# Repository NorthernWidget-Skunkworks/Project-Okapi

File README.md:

# Okapi: Data logger with integrated solar charging and modular telemetry

***Okapi data logger (Resnik v0.4.0), with a micro-SD card for local storage and a Particle Boron telemetry module.***

The **Okapi** data logger responds to the need for a robust, flexible, and power-efficient open-source option to record and transmit data from remote locations. It is programmable using the open-source standard Arduino framework via a standard micro-USB cable and supports a wide range of sensor input/output options. It connects to dual power supplies to ensure consistent recordings, and interfaces with a range of “Feather”-form-factor boards for telemetry.

## Namesake

The Okapi, a relative of the giraffe, communicates over long distances using [infrasound](https://en.wikipedia.org/wiki/Infrasound). The telemetry capabilities of this data logger inspired this namesake.

## Technical specifications

### Electronic Hardware

* Microcontroller (computer) core
  * ATMega1284p
  * Arduino compatible
  * Programmable using C++
  * 8 MHz
* Real-time clock
  * DS3231M
  * Temperature-compensated crystal for high accuracy (±5 ppm)
* Sensor and general-purpose connections
  * Primary Rail (selectable 3.3V or 5V)
    * I2C (up to 128 sensors permitted; expansion ports provided by Project Heptapod)
    * SPI
    * 2x 16-bit analog
    * Analog voltage reference
    * 12-bit Digital-to-analog conversion
    * 2x General-purpose input/output
    * USART
    * 2x Vbus (selectable 3.3V or 5V)
    * 2x Ground
  * Secondary Rail (selectable 3.3V or 5V)
    * I2C (up to 128 sensors permitted; expansion ports provided by Project Heptapod)
    * 2x 16-bit analog
    * 2x General-purpose input/output
    * USART
    * 2x Vbus (selectable 3.3V or 5V)
    * 2x Ground
* Data storage and return
  * Local storage: micro SD card
  * Telemetry: support for Feather-profile boards, including Particle devices:
    * Mobile phone networks
    * WiFi
    * Bluetooth
    * [In development] Iridium satellite
* Power
  * Dual power supply
  * Primary Power
    * Built-in maximum-power-point-tracking solar-charge-control circuitry
    * Lithium-Ion battery
  * Backup Power
    * Alkaline AA batteries
  * Real-time clock
    * Coin cell
  * Power consumption
    * Primary power, sleeping: 80 μA
    * Backup power, sleeping: 4 μA
    * Active (typical: data logger without sensors): 10 mA
    * Transmitting (mobile networks, typical: Particle Boron):
      * 16 mA background
      * 40 mA burst
  * Power generation
  * Solar, low light: 100 mA
* User interface
  * “Log” button: instantaneous reading (for testing)
  * “Reset” button
  * 2x 3-color indicator LEDs
  * Computer readout via a serial monitor, included in the Arduino software
* Open-source licensing via CC BY-SA 4.0

>> @bschulz1701: Any updates needed? I think that there is also a WDT (correct?)

### Electronic Software and Firmware

* Programmable using the Arduino IDE https://www.arduino.cc/en/main/software
* Custom bootloader and board definition for ATMega1284p available via https://github.com/NorthernWidget/Arduino_Boards
* Custom libraries from Northern Widget and the open-source community
  * Primary data-logger functions
  * Libraries available with each sensor, exposing a standard interface
* Open-source licensing via GNU GPL 3.0

### Pinout and board interfaces

***Okapi data logger (Resnik v0.4.0) with pins, connectors, and interactive items annotated.***

**Pins are colored following this convention:**
* Ground: black
* Power supply: red
* Universal Serial Asynchronous Receiver--Transmitter (USART or UART): blue
* General-purpose I/O pins: gray
* Analog inputs and associated reference voltage: green
* Digital communications buses (SPI and I2C): purple
* Analog adjustable voltage output: salmon

**The power and programming connectors at the "south" end of the board are as follows:**
* Micro-USB connector
  * The same connector as many Android and other mobile phones at the time of writing; may be programmed using any USB cable for these that is not charging-only (i.e. that can carry data)
  * Can be used with our [clock-setting program](https://github.com/NorthernWidget/SetTime_GUI) to set the time on the real-time clock.
  * Provides power to the data logger while it is connected; this power source is isolated from the batteries and solar panel, and therefore may be plugged in safely at any time.
* Solar panel, 4.95--32.0 V. A wide range of panels can work with this.
* Li-Ion battery, 2.60--4.475 V. This works with standard 18650 Li-ion batteries. It can work well with just a single battery, but if more storage is required, multiple 18650 batteries may be connected in parallel; we have a circuit-board design to do this: https://github.com/NorthernWidget/LiIon-18650-Parallel. ***CAUTION***: most commercially available multiple-18650-battery holders connect them in series; this voltage is ***TOO HIGH*** for the data logger.
* Primary batteries. This is ideally a pack of 3 primary (i.e., not reusable) Alkaline (or better) AA batteries with a long shelf life. The Okapi data logger will switch to these if its rechargeable power supply shuts down. The internal electronics reduce the quiescent power consumption while under backup power (see the above list of [electronic hardware technical specifications](#electronic-hardware)) and inform the logger about which power supply is being used, allowing it to, for example, reduce or temporarily terminate data transmission.

>> @bschulz1701: Solar panel supply current / size?

**"RST" and "LOG" buttons:**
* Reset ("RST"): stop the program that is currently executing on the main logger and return it to its boot sequence.
* Log Now ("LOG"): take a reading immediately. This is useful for diagnoses and testing.

>> General note: we may want to have an LED flash whenever the logger takes a reading -- even for 1/10 of a second. With an option to disable this, of course. But it is often better to know while in the field that a system is working

**Other notes, clockwise from the top:**
* The socket holds a [Feather-form-factor board](https://learn.adafruit.com/adafruit-feather/feather-specification).
  * This standard, designed by [Adafruit](https://www.adafruit.com/), has been widely adopted, including by the IoT/telemetry module designer [Particle](https://www.particle.io/).
  * We often use a [Particle Boron mobile-phone telemetry unit](https://docs.particle.io/boron/).
* Mounting holes for [\#4 screws](https://www.mcmaster.com/91772A106/)
* CR1220 battery; can power the real-time clock for up to 7 years
* ISP header (also called an ICSP header): This 3x2 header is used with an in-system programmer (in-circuit system programmer) to upload the (bootloader)[#installing-the-bootloader] to the data logger.
* A micro-SD card holds a copy of all data, whether or not any telemetry is used

>> @bschulz1701: check my clock 7-year figure

***Okapi data logger (Resnik v0.4.0) with key microchips, LEDs, and switches marked.*** *MCU: Microcontroller. RTC: Real-time clock. LED: Light-emitting diode. Bus: a subsystem for connections and data transfer.*

The Okapi data logger contains two buses (see above), each of which has an independent voltage. The primary bus is on the left and the secondary bus is on the right. These can be selected as 3.3V (switches slid towards the inside of the board) or 5V (switches towards the outside of the board).

>> @bschulz1701: How much power can each bus source/sink?

Two LEDs, status and auxiliary, flash messages to the user to provide information on proper operations vs. a variety of possible errors. These are useful for field diagnoses, and are further described in [the field guide section, below](#field-guide).

>> Design note: move STAT label to left of LED so it can be better seen

The Li-ion override button, which can be pressed with the tip of a pen or other small object, ...

>> @bschulz1701: This somehow overrides the Li-Ion battery electronics to allow something to happen... but I am not remembering what!

## On-board Devices

### I2C

| **Device**                                                        	| **Default address** 	| **Reprogrammable address** 	| **Function**                                                     	|
|-------------------------------------------------------------------	|---------------------	|----------------------------	|------------------------------------------------------------------	|
| [DS3231](https://github.com/NorthernWidget/DS3231_Logger)         	| 0x68                	| N                          	| Real-time clock                                                  	|
| [MCP23018](https://github.com/NorthernWidget-Skunkworks/MCP23018) 	| 0x20                	| N                          	| I/O Expander                                                     	|
| [ADS1115](https://github.com/adafruit/Adafruit_ADS1X15)           	| 0x48                	| N                          	| ADC (on-board devices)                                           	|
| [ADS1115](https://github.com/adafruit/Adafruit_ADS1X15)           	| 0x49                	| N                          	| ADC (off-board devices)                                          	|
| [MCP4725](https://github.com/NorthernWidget-Skunkworks/MCP4725)   	| 0x62                	| N                          	| DAC                                                              	|
| [BME280](https://github.com/NorthernWidget/BME_Library)           	| 0x77                	| N                          	| On-board barometric pressure, temperature, and relative humidity 	|

### SPI

* SD Card

### UART (USART)

* FTDI USB-Serial converter
* Feather form-factor telemetry board; typically [Particle Boron](https://docs.particle.io/boron/)

## Assembly

Assembling this data logger is possible by hand with sufficient skill and the following tools:
* Temperature-controlled soldering iron
* Hot-air rework station
* Equipment for stenciling with solder paste
* ESD-safe tweezers and workstation
* Solder wick

Mechanized assembly by a professional circuit-board assembly house, which is available in many parts of the world, may be preferred due to the complexity of this data logger board.

>> THOUGHT: I have basic instructions for assembly on the [Project Walrus](https://github.com/NorthernWidget-Skunkworks/Project-TPDH-Walrus) README; I will not reproduce these here just yet, as we might want to set up a separate assembly guide, mostly with good links to existing resources, since our writing something of this nature would be to reinvent the wheel.

## Programming

### Downloading and installing the Arduino IDE

Go to https://www.arduino.cc/en/main/software. Choose the proper IDE version for your computer. For Windows, we suggest the non-app version to have more control over Arduino; this might change in the future. You will have to add custom libraries, so the web version will not work (at least, as of the time of writing). Download and install the Arduino IDE. Open it to begin the next steps.

### Installing the bootloader

Before a data logger can receive programs via the convenient USB port, it must have a *bootloader* that tells it to expect to receive new programs that way.  You can read more about bootloaders in general here: https://www.arduino.cc/en/Hacking/Bootloader.

Because you can't upload the bootloader via USB, you use the 2x3-pin 6-pin ICSP (also called ISP) header with a special device called an "in-circuit system programmer" (or just "in-system programmer; yup, that's what the acronym stands for).

Many devices exist to upload a bootloader including:
* The official [AVR ISP mkII](http://ww1.microchip.com/downloads/en/DeviceDoc/Atmel-42093-AVR-ISP-mkII_UserGuide.pdf) (no longer produced but available used)
* Using an [Arduino as an ISP](https://www.arduino.cc/en/tutorial/arduinoISP)
* The versatile [Olimex AVR-ISP-MK2](https://www.olimex.com/Products/AVR/Programmers/AVR-ISP-MK2/open-source-hardware)
* The [Adafruit USBtinyISP](https://www.adafruit.com/product/46)

To upload the bootloader, do the following:

1. Open the Arduino IDE. If you have not yet installed the Northern Widget board definitions, find and install them here (instructions provided): https://github.com/NorthernWidget/Arduino_Boards
2. Select the desired board -- most likely ***ATMega1284p 8MHz*** under *Northern Widget Boards*.
3. Plug the data logger into your computer via a micro-USB cable to provide power.
4. Plug your ISP of choice into your computer (via a USB cable) and onto the 6-pin header. There are two ways to place it on; the header is aligned such that the ribbon cable should be facing away from the board while programming. If this fails without being able to upload, try flipping the header around.
5. Go to Tools --> Programmer and select the appropriate programmer based on what you are using.
6. Go to Tools --> Burn bootloader. Typically, within a few seconds, you learn whether you succeeded or failed. Hopefully it worked!

***Important note for Linux users:*** You must supply permissions to the Arduino IDE for it to be able to use the ICSP, or you will have to run it using `sudo`. The former option is better; the latter is easier in the moment.

***Note: Be sure to download and/or update drivers for your ISP.***

### Installing the requisite software libraries

>> @awickert: Add a full list of the requisite software to install; finish the firmware aggregator and use those directions (or the Arduino ones) to help users install that + sdfat. Include screenshots and host those directions at https://github.com/NorthernWidget-Skunkworks/Firmware-Aggregator.

### How to write a program

The below program is an example that you can copy and paste directly into the Arduino IDE in order to upload to your data logger. We'll walk you through what each piece of the code is and does.

#### Full program
```c++
/*
 * Okapi example: connected with a Walrus pressure--temperature sensor, often
 * used for water-level measurements, via the Longbow I2C/RS-485 translator.
 * Written by Bobby Schulz with a few comments added by Andy Wickert.
 */

#include "Okapi.h"
#include <TP_Downhole_Longbow.h>

TP_Downhole_Longbow Walrus; // Instantiate Walrus sensor; relict library name
Okapi Logger; // Instantiate data logger object

String Header = ""; // Information header; starts as an empty string
uint8_t I2CVals[1] = {0x22}; // I2C addresses of sensors

unsigned long UpdateRate = 60; // Number of seconds between readings

void setup() {
  Header = Header + Walrus.GetHeader();
  Logger.begin(I2CVals, sizeof(I2CVals), Header); // Pass header info to logger
  Init();
}

void loop() {
  Logger.run(Update, UpdateRate);
}

String Update()
{
  Init();
  delay(1500);
  return Walrus.GetString();
}

void Init()
{
  Walrus.begin(13, 0x22); // Instantiate Walrus (at address = 13)
                          // and Longbow Widget (at address = 0x22)
}
```

#### "Include" statements

```c++
#include "Okapi.h"
#include <TP_Downhole_Longbow.h>
```

These bring in the two code libraries involved, the former for the data logger and the latter for the sensors. This allows the user to access the classes and functions within these two libraries, as we will show in more detail below.

#### Instantiate a sensor object

```c++
TP_Downhole_Longbow Walrus; // Instantiate Walrus sensor; relict library name
Okapi Logger; // Instantiate data logger object
```

"Instantiating an object" means that we create our own specific versions of the a class of items. This can be thought of as: `Breakfast myBreakfast`. Breakfast is the general concept, but I create "myBreakfast", which I can then modify. In this same way, "Logger" is what we call our Okapi data logger, and "Walrus" is what we call our "TP_Downhole_Longbow" sensor; this name is a holdover from an earlier design that is the ancestor of the Walrus. We can then access functions and variables within these two instantiated objects.

#### Declare the header string

```c++
String Header = ""; // Information header; starts as an empty string
```

We start with an empty header, but will soon add information to it.

#### Create a list of the I2C addresses of the sensors

```c++
uint8_t I2CVals[1] = {0x22}; // I2C addresses of sensors
```

This is the trickiest step. You need to know what the I2C address of your sensor is. You can skip this, but then the logger will not run a check to see if the sensor is properly connected.

>> Let's make sure that we record this one each page, or find a way to replace this.

#### Declare the amount of time between logging events

```c++
unsigned long UpdateRate = 60; // Number of seconds between readings
```

This is the number of seconds between logging events. If it takes 2 seconds to record data, make sure that you give the logger at least 3 seconds between events. The maximum logging time is set by the watchdog timer, which [FINISH HERE]

>> @BSCHULZ1701: Is there an external WDT on Okapi?

#### `setup()` step: runs once at the start

```c++
void setup() {
  Header = Header + Walrus.GetHeader();
  Logger.begin(I2CVals, sizeof(I2CVals), Header); //Pass header info to logger
  Init();
}
```

`setup()` is a special function that runs just once when the logger boots up. In this case, it first adds the Walrus' header to the header string. `GetHeader()` is a standard function that lies within each of our sensor libraries and returns this header information as a `String`. We then pass the header and the I2C values to the Okapi library's `begin()` function. This sets up the header and prepares the data loger to record data. Finally, this function calls `Init()`, which we skip ahead to describe immediately below.

>> (awickert): I still don't understand why we have to pass `sizeof()` and can't just compute that within the function.

#### `Init()` function: skipping ahead to understand `setup()`

```c++
void Init()
{
  Walrus.begin(13, 0x22); // Instantiate Walrus (at address = 13)
                          // and Longbow Widget (at address = 0x22)
}
```

The `Init()` function calls the `begin()` function, standard within each Northern Widget sensor library, to instantiate the connection ports (e.g., I2C, RS-485) used to communicate between the sensor and the logger. In this case, there is only one sensor, but two ports are needed: An RS-485 signal goes from the Walrus to the Longbow Widget, which then converts the signal into an I2C signal with its own address. The reason for this is that an I2C signal can travel only ~3 m, but an RS-485 signal can travel ~100 m.

#### `loop()` step: keeps running until stopped

```c++
void loop() {
  Logger.run(Update, UpdateRate);
}
```

The loop calls the main function of the Okapi library, `run()`, repeatedly. This puts the logger into a low-power sleep mode and wakes it up only when interrupted by the clock or the "LOG" button. `Update` refers to the function described immediately below. `UpdateRate` is our logging interval defined above.

#### `Update()` function: Gives data for the logger to record

```c++
String Update()
{
  Init();
  delay(1500);
  return Walrus.GetString();
}
```

The `Update()` function first calls the `Init()` function to be sure that the sensor is ready to log. It then in this case delays 1500 milliseconds; this is an ad-hoc solution to the question of how long it takes the pressure transducer to settle after being started up, and is a safe large amount of time. This function then can `return` a string of all of the Walrus' readings (one pressure and two temperature measurements) separated by commas. This is then concatenated to a list of logger-internal measurements -- date/time; on-board temperature, pressure, and relative humidity; and onboard voltages for battery and solar-panel status -- and recorded to the SD card. If telemetry were present, these data could also be sent to a remote location.

### Reference

A full index of the public variables and functions within the Okapi data logger library is available at https://github.com/NorthernWidget/Okapi_Library.

>> Send user to library page

>> Thoughts: We should make all comments compatible with doxygen (following) what I did with the ALog library. It also looks like TravisCI has support for Arduino(!) This means that we could also automate construction of the documentation for these libraries.

### Integration with Particle Boron

>> @bschulz1701?

## Wiring

>> Example needed

## Power supply

* **Lithium-ion 18650 rechargeable batteries**; this board can hold two in parallel: https://github.com/NorthernWidget/LiIon-18650-Parallel
* **Solar panel**. A wide range is acceptable, but we like [Voltaic Systems' 6-watt panel](https://voltaicsystems.com/6-watt-panel/). If you do not want to snip off the barrel jack, [this extension plug from Adafruit should work](https://www.adafruit.com/product/2788) (though we have not tested it... and you'll also have to cut *it* in half).
* **Primary alkaline batteries**; we typically use three high-quality (e.g., Duracell) AAs. These are the backup power supply, and we place them in a [3xAA holder (in series for the proper voltage) with a switch](https://www.jameco.com/z/SBH-331-AS-R-3x-AA-Battery-Holder-with-Cover-and-Switch_216144.html).

>> @bschulz1701: new smarter 18650 holder?

## Housing

The below suggestions encompass what we use and suggest for the housing. In the end, any sufficiently waterproof enclosure will work.

### Materials

* **Enclosure**: [PolyCase WH-16-03 outdoor-rated hinged enclosure](https://www.polycase.com/wh-16)
* **Cable glands**: [RDC07AA](https://www.elecdirect.com/catalogsearch/result/?q=RDC07AA). One per sensor, plus one for the solar panel.
>> AW: Photo didn't take; look up
* **Fasteners**
  * [M5-0.8 x 10 mm truss head screws](https://www.mcmaster.com/92467A320/) x4 to attach mounting plate to threaded inserts in the enclosure
  * [\#4-40 x 1/4 in pan head screws](https://www.mcmaster.com/91772A106/) x22 to attach Okapi, battery packs, and mounting plate to standoffs
  * [\#4-40 x 2 in Female Threaded Hex Standoffs](https://www.mcmaster.com/91115A173/) x3 to stand off Okapi from mounting plate
  * [\#4-40 x 1/2 in Female Threaded Hex Standoffs](https://www.mcmaster.com/91920A533/) x8 to stand off AA battery pack and Li-Ion battery pack from mounting plate
* **Mounting plate for Okapi** (Milled, ABS)
  * [Mounting Plate Design](Mounting%20Plate)
* **Power**
>> Solar panel
  * [3x AA battery pack BK-1280-PC6](https://www.digikey.com/en/products/detail/mpd-memory-protection-devices/BK-1280-PC6/1640076) for alkaline battery backup, mounting holes included for #4-40 screws
>> Li-Ion battery and holder

### Tools

* CNC mill and/or drill press
* Deburring tool or knife + skill and patience
* Torque wrench(es) for 1.0, 1.2 N m

### Assembly

>> Guide with photos. Perhaps ask @superchap123 to use his CNC

>> Placeholder for Now

>> Also include information on passing wiring through

## Field operator's guide

### Initialize
1. Ensure that all connections are secure and SD card is inserted
2. Turn battery pack on
3. Wait for GREEN - GREEN - 5x Blue Flash
	- If you see this, the logger is properly recording data. To double-check, go to "Check"
	- If you see a different flash pattern, go to "Error"

### Check
1. After going through "Initialize", wait 2-3 minutes
2. Follow the instructions in the "Download" section
3. Check to make sure that all the data are being recorded at the proper (UTC) time
4. Check that valid values are being recorded for sensors
7. Whether or not files are properly recorded, return to "Initialize"
	- If files are not recorded, replace the SD card, check all connections, turn the logger back
	  on, and try again
	- If there is an issue with a specific sensor, check connections and troubleshoot
	- If files are recorded properly, return to Initilaize and do not return to "Check"

### SD card swap
1. Turn battery pack off
2. Remove SD card. Ensure that it is labeled. Put it somewhere safe and memorable
3. Replace the SD card with an equivalently labeled SD card
4. Go to "Initialize"

### Download
1. Turn battery pack off
2. Remove SD card
3. Insert SD card in computer
4. Navigate in the SD card to the most recent "log" file (NW→<serial_number>→Log<number>.txt)
5. Save the data file in a well-labeled and organized place.
6. Safely eject the SD card from the computer
7. Go to "Initialize"

### Error

#### Status Codes

The first LED (AUX) will turn green so long as power is applied.
The second LED (STAT) will have one of the colors below.

**Green:**: All systems check out OK, logging will proceed

**Orange:**: A sensor system is not registering properly, some sensor data may be missing or incorrect
* Verify correct polarity of sensor connection
* Ensure the right sensor is connected
* Verify the screw terminals are well connected to the wires (a loose connection can cause a failure)
* Make sure battery power is applied, some sensors can fail otherwise

**Cyan:**: Clock time is incorrect, but logger is otherwise working correctly
* Connect the logger to a computer and reset the clock using the Northern Widget Time Set GUI
* Start Processing
* Open the Northern Widget Time Set program
* Note and record the wrong time if the logger has been out in the field, alongside the current (correct) time, to correct the prior measurements
* Click the "set time" button and check that you are <3 seconds off of the correct time
* Click the "close" button

**Pink**: (looks like purple to some people): SD card is not inserted
* Insert the SD card, or remove and re-insert to make sure card is fully seated

**Red**: Critical on board component is not functioning correctly, such as SD card or clock; Logging will likely not be able to proceed
* Attempt power cycle
* Try different SD card
* Disconnect all sensors; reconnect one by one and check

**Yellow, Fast Blinking**: <50% battery capacity
* Replace batteries: turn battery pack off, replace batteries, and turn battery pack back on

**Red, Fast Blinking**: Batteries <3.3V. Voltage too low to properly function
* Replace batteries: turn battery pack off, replace batteries, and turn battery pack back on.

#### General tips to solve many kinds of errors
* Turn the the logger off and on
* Verify the quality of all screw terminal connections by gently tugging on the wires and making sure they stay in place, if not, remove, replace, and re-tighten the connection
* Ensure sensors and/or cables are not damaged, this can result is shorts or other problems
* Make sure batteries have sufficient voltage to run the logger (>3.3 V)

## NW-Device-Specification schema

Okapi's serial number scheme is [Schema 0](https://github.com/NorthernWidget/NW-Device-Specification) — the same 8-byte EEPROM block used by Margay, predating the formal specification. Schema 1 formalizes it as Page 0 and defines a putative Page 1 for the case where Okapi communicates its status to a higher-level device (e.g., the Particle Boron telemetry board). **Okapi has no current peripheral interface; Page 1 is hypothetical.**

Over I²C this would follow the standard register-addressed read. Over UART (the current Okapi↔Boron link) a framing layer is required; see the [NW-Device-Specification transport section](https://github.com/NorthernWidget/NW-Device-Specification) for the Magic Preamble and COBS options.

### Current EEPROM serial number (Schema 0)

Eight bytes at `EEPROM[length−8]` through `EEPROM[length−1]`, big-endian uint16 per field, written by the setup sketch `SN Set` command — identical scheme to Margay:

| Bytes | Field | Example (Okapi v1.0) |
|-------|-------|----------------------|
| 0–1 | Board type | `0x4F01` (`'O'` = 0x4F, revision 1) |
| 2–3 | Group ID | operator-assigned |
| 4–5 | Unique ID | monotonically increasing |
| 6–7 | FirmwareID | `0x0000` (hardcoded) |

Legacy units manufactured as "Resnik" carry board type `0x9950`.

### Proposed register layout (NW-Device-Specification Schema 1)

**Page 0 (0x00–0x1F) — Identity (EEPROM)**

```
Block 0 (0x00–0x07)   Core identity
  0x00        0x01                          Schema (NW-Device-Specification v1)
  0x01–0x05   'O','k','a','p','i'           Device name (5 bytes)
  0x06–0x07   0x00,0x00                     Reserved

Block 1 (0x08–0x0F)   Version
  0x08        HW major
  0x09        HW minor
  0x0A        FW patch
  0x0B–0x0D   0x00,0x00,0x00               Unused (combined repo convention)
  0x0E–0x0F   0x00,0x00                    Reserved

Block 2 (0x10–0x17)   Serial number
  0x10–0x11   0x4F,0x01                    Board type ('O'=0x4F, revision index)
  0x12–0x13   [manufacture]                Group ID
  0x14–0x15   [manufacture]                Unique ID
  0x16–0x17   0x00,0x00                    FirmwareID (legacy, reserved)

Block 3 (0x18–0x1F)   Integrity + administration
  0x18–0x1C   0x00 ×5                      Reserved
  0x1D        0x00                         Magic byte (reserved; purpose TBD)
  0x1E        [computed]                   CRC-8 of bytes 0x00–0x1D
  0x1F        0x00                         Peripheral address (unassigned;
                                           Okapi is currently controller only)
```

**Page 1 (0x20–0x3F) — Logger status (SRAM) — HYPOTHETICAL**

Okapi is currently an I²C controller communicating with the Particle Boron via UART; it has no peripheral interface. This layout is proposed for the case where Okapi reports status to the Boron (or any higher-level device) using the NW schema. A natural peripheral address would be `0x4F` (ASCII `'O'`).

Okapi's dual power system (LiPo primary + solar charging + AA backup) differs from Margay. Full power monitoring signals are not yet implemented in the library (`GetPowerStats()` is reserved); fields marked TBD will be defined when that work is completed.

```
Block 0 (0x20–0x27)   System status + power
  0x20        Status       bit 0=ready, bit 1=SD fault, bit 2=RTC fault,
                           bit 3=onboard fault, bit 4=sensor fault,
                           bit 5=LiPo warning, bit 6=LiPo error,
                           bit 7=backup warning
  0x21        LiPo %       uint8, 0–100
  0x22–0x23   LiPo voltage uint16, 0.01 V
  0x24–0x25   Solar input  uint16, TBD (V or mW pending GetPowerStats() impl.)
  0x26–0x27   Backup volt  uint16, 0.01 V (AA backup rail)

Block 1 (0x28–0x2F)   BME280 — onboard environment
  0x28–0x29   Temperature  int16, 0.01 °C
  0x2A–0x2B   Humidity     uint16, 0.01 %RH
  0x2C–0x2F   Pressure     uint32, 0.01 hPa

Block 2 (0x30–0x37)   DS3231M — RTC
  0x30–0x33   Timestamp    uint32, Unix time (seconds since 1970-01-01 UTC)
  0x34–0x35   Temperature  int16, 0.01 °C
  0x36–0x37   Reserved

Block 3 (0x38–0x3F)   Logger state
  0x38–0x39   Ext interrupts  uint16, accumulated count
  0x3A–0x3B   Log file #      uint16
  0x3C–0x3F   Log interval    uint32, seconds
```

No Page 2. Calibration constants are hardcoded in the library.

## Development namesake

Designing a large-platform, multi-power-system, and telemetry-enabled data logger is the single most complex task that our group has undertaken. Bobby Schulz, lead engineer, code-named the dev version of this work "Project Resnik", after Dr. Judy Resnik, electrical engineer and astronaut. Although we don't have to manage the complexities of space travel, we think that our design will do pretty well down here on Planet Earth.

## Acknowledgments

Support for this project provided by:

<br/>
<br/>
<br />This work is licensed under a <a rel="license" href="http://creativecommons.org/licenses/by-sa/4.0/">Creative Commons Attribution-ShareAlike 4.0 International License</a>.

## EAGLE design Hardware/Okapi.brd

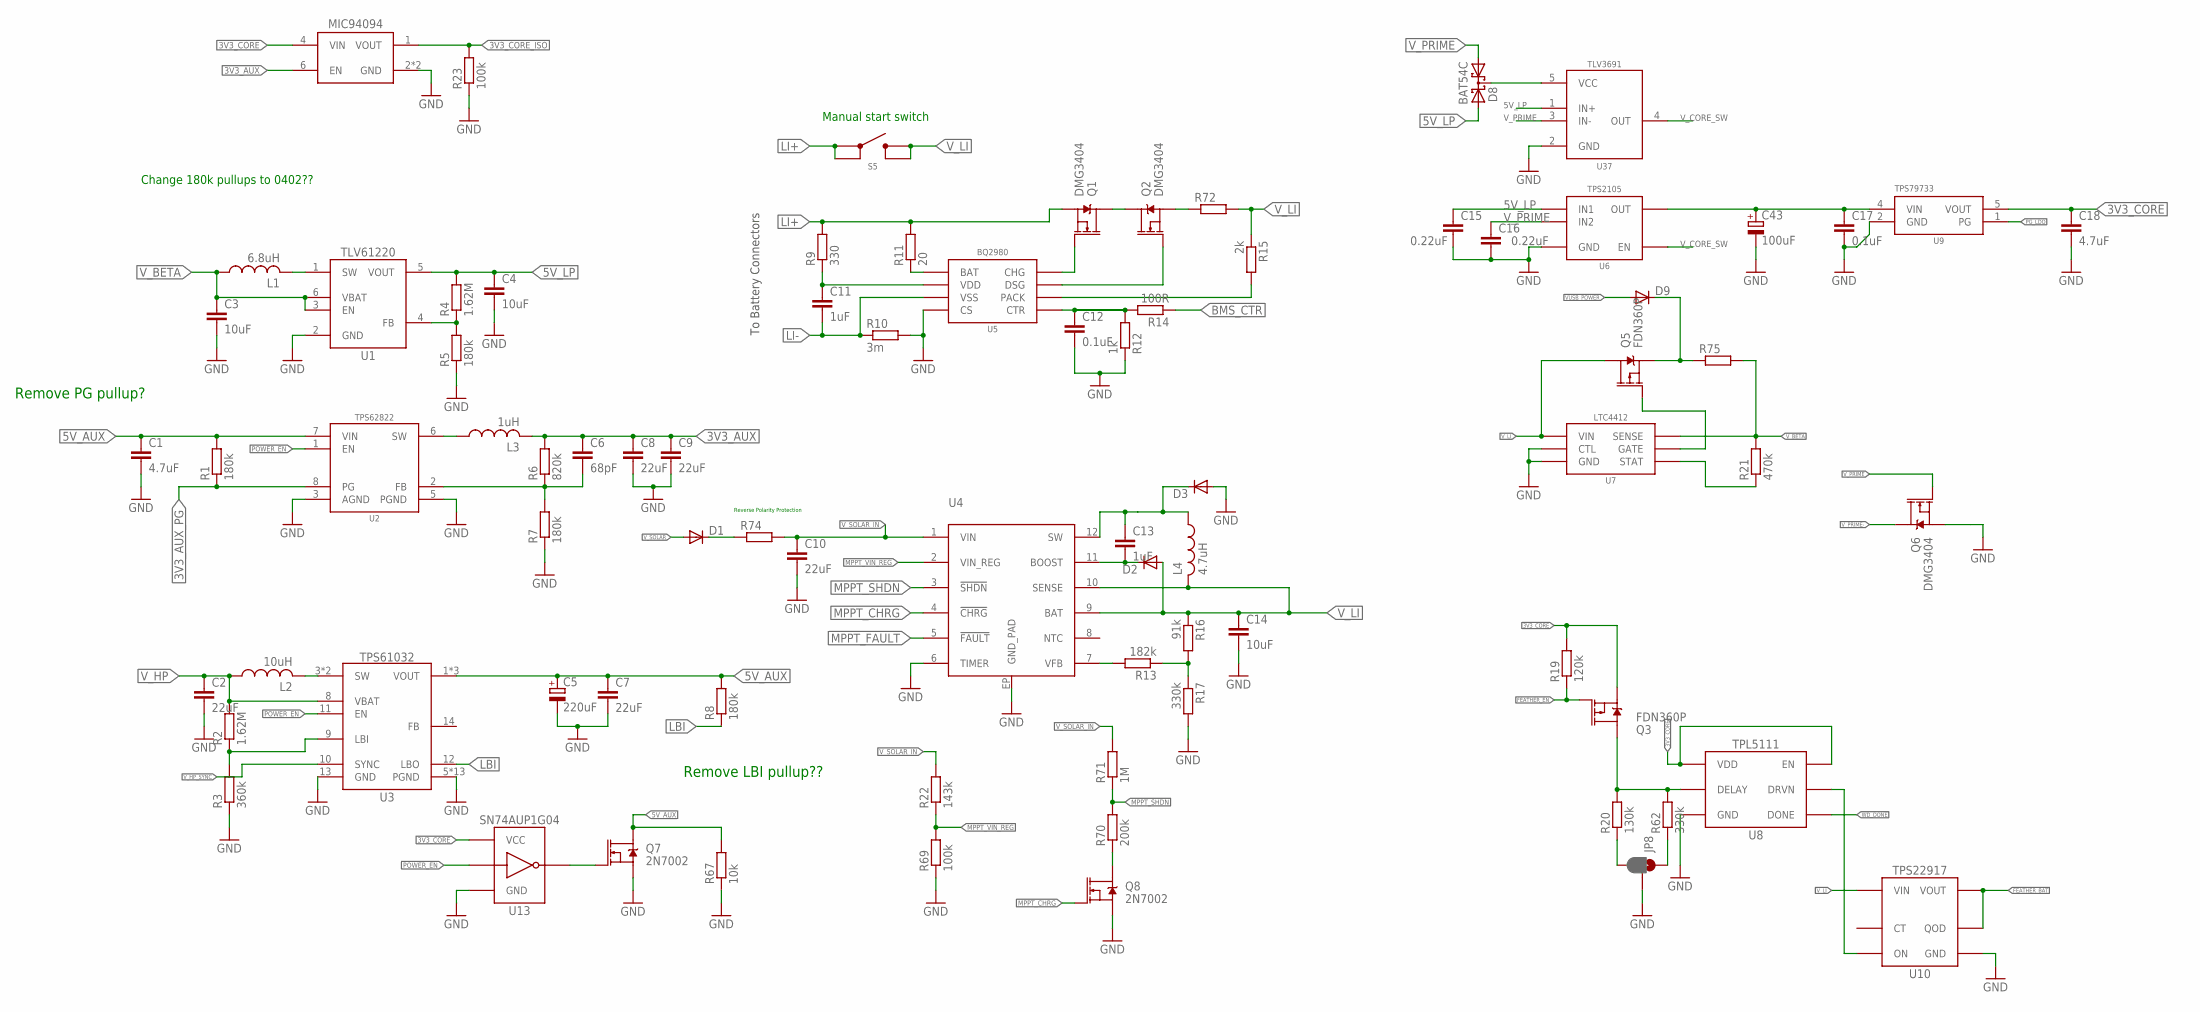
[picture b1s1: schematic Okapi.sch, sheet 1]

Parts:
C1: 4.7uF; C0805
C2, C7, C8, C9, C10: 22uF; C0805
C3, C4, C14: 10uF; C0805
C5: 220uF; C2917; MPN TPSY227K010R0100; DIGIKEY 478-5408-1-ND
C6: 68pF; C0402
C11, C13: 1uF; C0603
C12, C17: 0.1uF; C0402
C15, C16: 0.22uF; C0402
C18: 4.7uF; C0603
C43: 100uF; C1206_TANT; MPN TL8A0107M010D; DIGIKEY 718-1921-1-ND
D1, D3: DIODEDO-214AC; DO214AC; MPN CMSH3-40MA TR13; DIGIKEY CMSH3-40MATR13CT-ND
D2: DIODESOD-323; SOD323-R; MPN CMDSH2-3 TR; DIGIKEY CMDSH2-3CT-ND
D8: BAT54C; SOT23-3@1
D9: DIODEDO-214AC; DO214AC; MPN B340A-13-F; DIGIKEY B340A-FDICT-ND
JP8: JUMPER-SMT_3_1-NC_PASTE_SILK; SMT-JUMPER_3_1-NC_PASTE_SILK
L1: 6.8uH; 1008; MPN 74438323068; DIGIKEY 732-4849-1-ND
L2: 10uH; WE-XHMI(6.65X6.45); MPN 74439346100; DIGIKEY 732-10707-1-ND
L3: 1uH; WE-LQS(3X3); MPN 74404032010; DIGIKEY 732-5491-1-ND
L4: 4.7uH; WE-MAIA(4.1X4.1); MPN 78438356047; DIGIKEY 732-11316-1-ND
Q1, Q2, Q6: DMG3404; SOT23-3
Q3, Q5: FDN360P; SOT23-3@1
Q7, Q8: 2N7002; SOT323
R1, R5, R7, R8: 180k; R0603
R2, R4: 1.62M; R0603
R3: 360k; R0603
R6: 820k; R0603
R9: 330; R0402
R10: 3m; R0805
R11: 20; R0402
R12: 1k; R0402
R13: 182k; R0603
R14: 100R; R0402
R15: 2k; R0402
R16: 91k; R0603
R17, R62: 330k; R0603
R19: 120k; R0402
R20: 130k; R0603
R21: 470k; R0603
R22: 143k; R0603
R23: 100k; R0402
R67: 10k; R0402
R69: 100k; R0603
R70: 200k; R0603
R71: 1M; R0603
R72, R74, R75: R-EU_R0805; R0805
S5: BUTTON2.6X1.6; SWITCH_2.6X1.6; MPN EVP-BB2A9B000; DIGIKEY P19888CT-ND
U1: TLV61220DBV; DBV_R-PDSO-G6
U2: TPS62822DLC; DLC_8
U3: TPS61032RSA; RSA_S-PVQFN-N16
U4: LT3652DD; DFN_12_3X3
U5: BQ2980RUG; RUG_S-PQFP-N8
U6: TPS2105; SOT23-5
U7: LTC4412S6; SOT23-6L
U8: TPL5111DDC; DDC_R-PDSO-G6
U9: TPS79733; DCK_R-PDSO-G5
U10: TPS22917DBV; DBV_R-PDSO-G6
U13: SN74AUP1G04YFP; DSBGD_4
U37: TLV3691DCK; DCK_R-PDSO-G5
U39: MIC94094C6; SC-70_6

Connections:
3V3_AUX: C6.1, C8.1, C9.1, L3.P$2 (2), R6.2, U39.6 (EN); also elsewhere on the board
3V3_AUX_PG: R1.1, U2.8 (PG); also elsewhere on the board
3V3_CORE: C18.1, Q3.2 (S), R19.2, U8.1 (VDD), U8.6 (EN), U9.5 (VOUT), U13.A2 (VCC), U39.4 (VIN); also elsewhere on the board
3V3_CORE_ISO: R23.2, U39.1 (VOUT); also elsewhere on the board
5V_AUX: C1.1, C5.+, C7.1, Q7.3 (D), R1.2, R8.2, R67.2, U2.7 (VIN), U3.1 (VOUT), U3.15 (VOUT), U3.16 (VOUT); also elsewhere on the board
5V_LP: C4.1, C15.1, D8.2 (A2), R4.2, U1.5 (VOUT), U6.5 (IN1), U37.1 (IN+)
BMS_CTR: R14.1; also elsewhere on the board
FEATHER_BAT: U10.5 (QOD), U10.6 (VOUT); also elsewhere on the board
FEATHER_EN: Q3.1 (G), R19.1; also elsewhere on the board
GND: C1.2, C2.2, C3.2, C4.2, C5.-, C7.2, C8.2, C9.2, C10.2, C12.2, C14.2, C15.2, C16.2, C17.2, C18.2, C43.-, D3.A, JP8.2, Q6.2 (S), Q7.2 (S), Q8.2 (S), R3.1, R5.1, R7.1, R10.2, R12.1, R17.2, R23.1, R67.1, R69.1, U1.2 (GND), U2.3 (AGND), U2.5 (PGND), U3.5 (PGND), U3.6 (PGND), U3.7 (PGND), U3.13 (GND), U3.PAD (PGND), U3.PAD@1 (PGND), U3.PAD@2 (PGND), U3.PAD@3 (PGND), U3.PAD@4 (PGND), U3.PAD@5 (PGND), U3.PAD@6 (PGND), U3.PAD@7 (PGND), U3.PAD@8 (PGND), U3.PAD@9 (PGND), U4.6 (TIMER), U4.EP (GND_PAD), U5.4 (CS), U6.2 (GND), U7.2 (GND), U7.3 (CTL), U8.2 (GND), U9.2 (GND), U10.2 (GND), U13.B1 (GND), U37.2 (GND), U39.2 (GND), U39.5 (GND); also elsewhere on the board
LBI: R8.1, U3.12 (LBO); also elsewhere on the board
LI+: Q1.2 (S), R9.2, R11.2, S5.A (1), S5.A' (2); also elsewhere on the board
LI-: C11.2, R10.1, U5.3 (VSS); also elsewhere on the board
MPPT_CHRG: Q8.1 (G), U4.4 (!CHRG); also elsewhere on the board
MPPT_FAULT: U4.5 (!FAULT); also elsewhere on the board
MPPT_SHDN: R70.2, R71.1, U4.3 (!SHDN)
MPPT_VIN_REG: R22.1, R69.2, U4.2 (VIN_REG)
unnamed: L3.P$1 (1), U2.6 (SW)
unnamed: C6.2, R6.1, R7.2, U2.2 (FB)
unnamed: R2.1, R3.2, U3.9 (LBI)
unnamed: L2.2, U3.3 (SW), U3.4 (SW)
unnamed: Q1.3 (D), Q2.3 (D)
unnamed: R4.1, R5.2, U1.4 (FB)
unnamed: Q1.1 (G), U5.8 (CHG)
unnamed: L1.2, U1.1 (SW)
unnamed: Q2.1 (G), U5.7 (DSG)
unnamed: R15.2, U5.6 (PACK)
unnamed: R13.1, R16.2, R17.1
unnamed: C12.1, R12.2, R14.2, U5.5 (CTR)
unnamed: R11.1, U5.1 (BAT)
unnamed: R13.2, U4.7 (VFB)
unnamed: C11.1, R9.1, U5.2 (VDD)
unnamed: C13.2, D2.C, U4.11 (BOOST)
unnamed: JP8.3, R20.1
unnamed: C13.1, D3.C, L4.P$1 (1), U4.12 (SW)
unnamed: Q8.3 (D), R70.1
unnamed: JP8.1, R62.1
unnamed: Q5.1 (G), U7.5 (GATE)
unnamed: R21.1, U7.4 (STAT)
unnamed: Q3.3 (D), R20.2, R62.2, U8.3 (DELAY)
unnamed: U8.5 (DRVN), U10.3 (ON)
unnamed: Q7.1 (G), U13.B2 (Y)
unnamed: D8.3 (C), U37.5 (VCC)
PG_LDO: U9.1 (PG); also elsewhere on the board
POWER_EN: U2.1 (EN), U3.11 (EN), U13.A1 (A); also elsewhere on the board
VUSB_POWER: D9.A; also elsewhere on the board
V_BETA: C3.1, L1.1, R21.2, R75.2, U1.3 (EN), U1.6 (VBAT), U7.6 (SENSE); also elsewhere on the board
V_BETA_SENSE: D9.C, Q5.2 (S), R75.1; also elsewhere on the board
V_CORE: C17.1, C43.+, U6.4 (OUT), U9.4 (VIN)
V_CORE_SW: U6.1 (EN), U37.4 (OUT)
V_HP: C2.1, L2.1, R2.2, U3.8 (VBAT); also elsewhere on the board
V_HP_SYNC: U3.10 (SYNC); also elsewhere on the board
V_LI: C14.1, D2.A, L4.P$2 (2), Q5.3 (D), R15.1, R16.1, R72.2, S5.B (3), S5.B' (4), U4.9 (BAT), U4.10 (SENSE), U7.1 (VIN), U10.1 (VIN); also elsewhere on the board
V_LI_SENSE: Q2.2 (S), R72.1; also elsewhere on the board
V_PRIME: C16.1, D8.1 (A1), Q6.1 (G), U6.3 (IN2), U37.3 (IN-); also elsewhere on the board
V_PRIME-: Q6.3 (D); also elsewhere on the board
V_SOLAR: D1.A; also elsewhere on the board
V_SOLAR_IN: C10.1, R22.2, R71.2, R74.2, U4.1 (VIN); also elsewhere on the board
V_SOLAR_SENSE: D1.C, R74.1; also elsewhere on the board
WD_DONE: U8.4 (DONE); also elsewhere on the board

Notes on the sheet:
To Battery Connectors
Change 180k pullups to 0402??
Reverse Polarity Protection
Remove PG pullup?
Remove LBI pullup??
Manual start switch

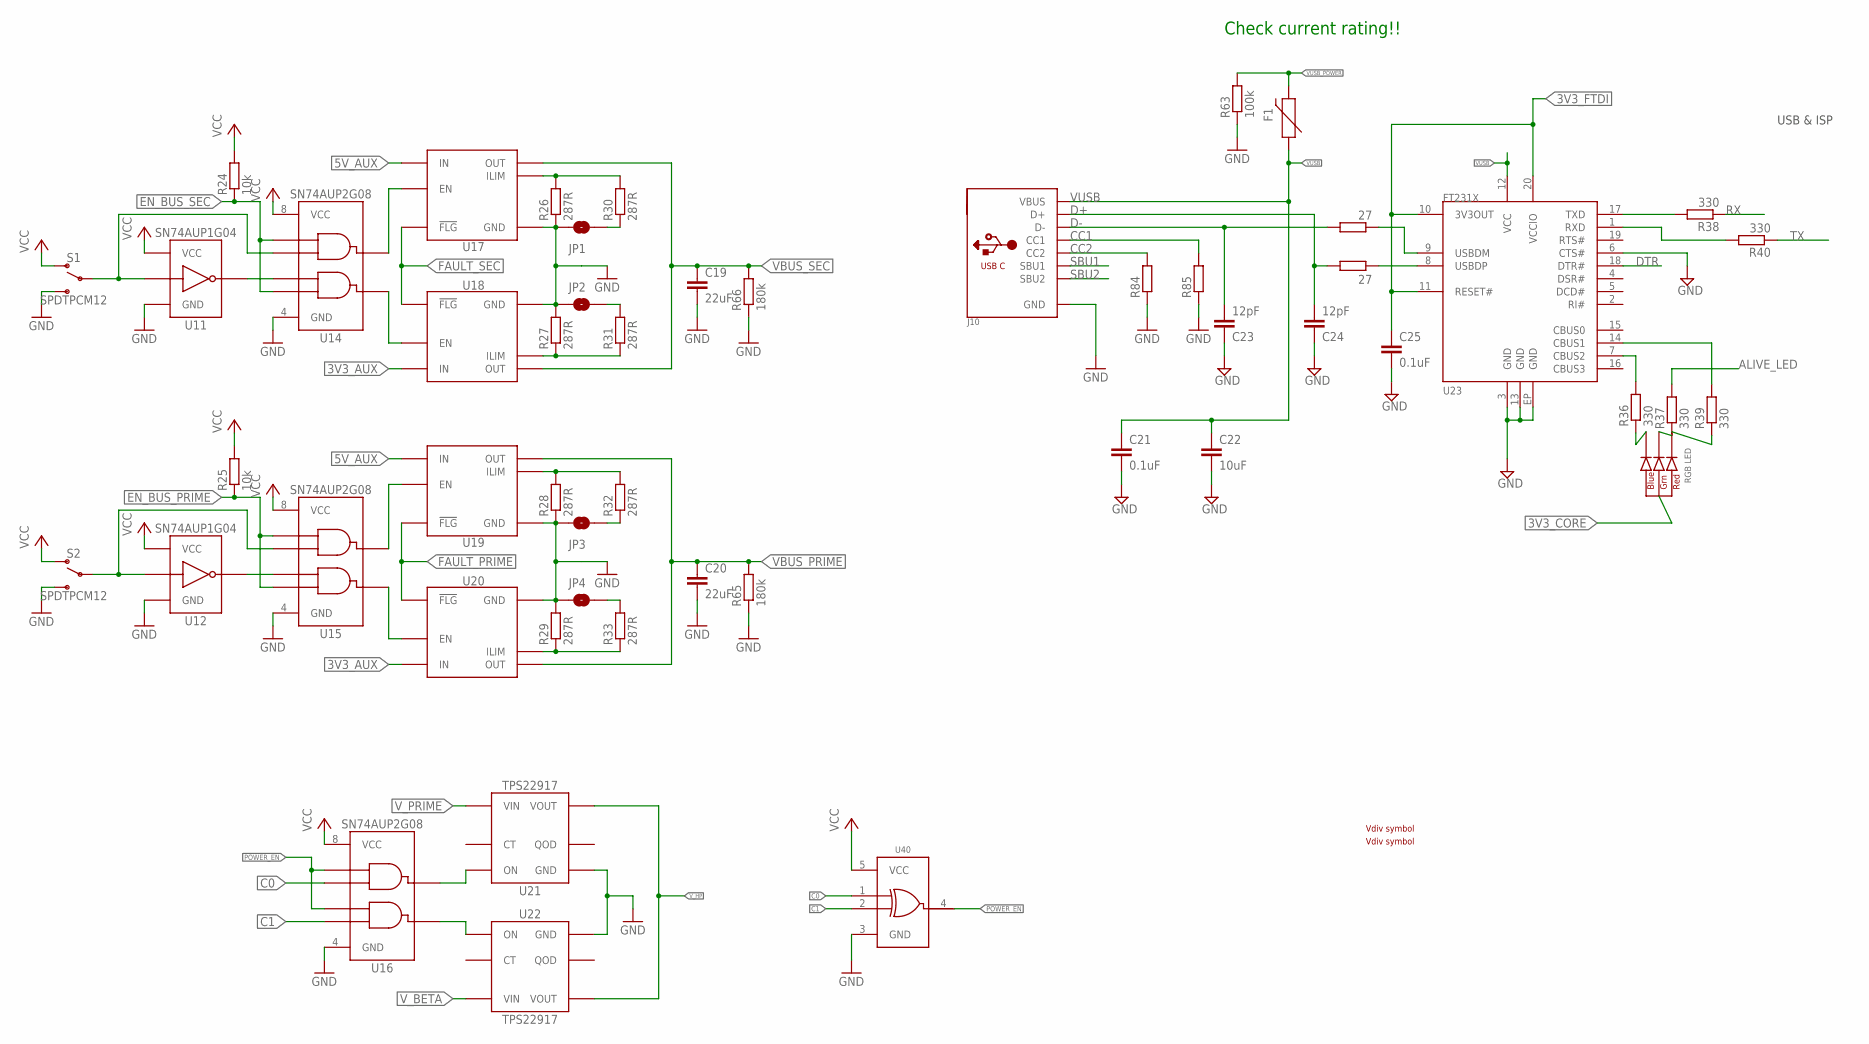
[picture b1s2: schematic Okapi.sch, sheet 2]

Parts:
C19, C20: 22uF; C0805
C21, C25: 0.1uF; C0402
C22: 10uF; C0805
C23, C24: 12pF; C0402
D4: CLVBA-FKA
F1: PPTC1.5A; 1206
J10: USB_C; USB_C_CUSB31-CFM2AX-01-X; MPN USB4105-GF-A; DIGIKEY 2073-USB4105-GF-ACT-ND
JP1, JP2, JP3, JP4: JUMPER-SMT_2_NO_SILK; SMT-JUMPER_2_NO_SILK
R24, R25: 10k; R0402
R26, R27, R28, R29, R30, R31, R32, R33: 287R; R0402
R34, R35: 27; R0402
R36, R38, R40: 330; R0402; MPN RC0603FR-07330RL
R37, R39: 330; R0402; MPN RC0603FR-07330RL; DIGIKEY 311-330HRCT-ND
R63: 100k; R0402
R65, R66: 180k; R0402
R84, R85: R-EU_5.1KR0402; R0402
S1, S2: SPDTPCM12; PCM12
U11, U12: SN74AUP1G04YFP; DSBGD_4
U14, U15, U16: SN74AUP2G08DQE; DQE_R-PX2SON-N8
U17, U18, U19, U20: MIC2544MSOP; MSOP_8
U21, U22: TPS22917DBV; DBV_R-PDSO-G6
U23: FT231X-Q; QFN20
U40: SN74AHC1G86DCK; DCK_R-PDSO-G5
U$1, U$2: VDIV-JP; VDIV_GENERIC

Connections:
3V3_AUX: R24.2, R25.2, S1.1 (O), S2.1 (O), U11.A2 (VCC), U12.A2 (VCC), U14.8 (VCC), U15.8 (VCC), U18.7 (IN), U20.7 (IN); also elsewhere on the board
3V3_CORE: D4.2 (ANODE), U16.8 (VCC), U40.5 (VCC); also elsewhere on the board
3V3_FTDI: C25.1, U23.10 (3V3OUT), U23.11 (RESET#), U23.20 (VCCIO)
5V_AUX: U17.7 (IN), U19.7 (IN); also elsewhere on the board
ALIVE_LED: R37.2; also elsewhere on the board
C0: U16.2 (B1), U40.1 (A); also elsewhere on the board
C1: U16.6 (B2), U40.2 (B); also elsewhere on the board
CC1: J10.A5 (CC1), R85.2
CC2: J10.B5 (CC2), R84.2
D+: C24.2, J10.A6 (D+), J10.B6 (D+), R35.2
D-: C23.2, J10.A7 (D-), J10.B7 (D-), R34.2
DTR: U23.18 (DTR#); also elsewhere on the board
EN_BUS_PRIME: R25.1, U15.1 (A1), U15.6 (B2); also elsewhere on the board
EN_BUS_SEC: R24.1, U14.1 (A1), U14.6 (B2); also elsewhere on the board
FAULT_PRIME: U19.2 (!FLG), U20.2 (!FLG); also elsewhere on the board
FAULT_SEC: U17.2 (!FLG), U18.2 (!FLG); also elsewhere on the board
GND: C19.2, C20.2, C21.2, C22.2, C23.1, C24.1, C25.2, J10.A1B12 (GND), J10.B1A12 (GND), JP1.1, JP2.1, JP3.1, JP4.1, R26.1, R27.2, R28.1, R29.2, R63.1, R65.1, R66.1, R84.1, R85.1, S1.3 (S), S2.3 (S), U11.B1 (GND), U12.B1 (GND), U14.4 (GND), U15.4 (GND), U16.4 (GND), U17.3 (GND), U18.3 (GND), U19.3 (GND), U20.3 (GND), U21.2 (GND), U22.2 (GND), U23.3 (GND), U23.6 (CTS#), U23.13 (GND), U23.EP (GND), U40.3 (GND); also elsewhere on the board
unnamed: U16.7 (Y1), U21.3 (ON)
unnamed: U16.3 (Y2), U22.3 (ON)
unnamed: U12.B2 (Y), U15.5 (A2)
unnamed: R28.2, R32.2, U19.5 (ILIM)
unnamed: S2.2, U12.A1 (A), U15.2 (B1)
unnamed: U15.7 (Y1), U19.1 (EN)
unnamed: U15.3 (Y2), U20.1 (EN)
unnamed: JP3.2, R32.1
unnamed: JP4.2, R33.2
unnamed: R29.1, R33.1, U20.5 (ILIM)
unnamed: U11.B2 (Y), U14.5 (A2)
unnamed: S1.2, U11.A1 (A), U14.2 (B1)
unnamed: U14.7 (Y1), U17.1 (EN)
unnamed: U14.3 (Y2), U18.1 (EN)
unnamed: R26.2, R30.2, U17.5 (ILIM)
unnamed: JP1.2, R30.1
unnamed: JP2.2, R31.2
unnamed: R27.1, R31.1, U18.5 (ILIM)
unnamed: R38.2, U23.17 (TXD)
unnamed: R40.2, U23.1 (RXD)
unnamed: R35.1, U23.8 (USBDP)
unnamed: R39.2, U23.14 (CBUS1)
unnamed: R34.1, U23.9 (USBDM)
unnamed: D4.1 (RED_CATH), R39.1
unnamed: D4.3 (BLUE_CATH), R36.1
unnamed: D4.4 (GREEN_CATH), R37.1
unnamed: R36.2, U23.7 (CBUS2)
POWER_EN: U16.1 (A1), U16.5 (A2), U40.4 (Y); also elsewhere on the board
QOD: U21.5 (QOD), U22.5 (QOD)
RX: R38.1; also elsewhere on the board
SBU1: J10.A8 (SBU1)
SBU2: J10.B8 (SBU2)
TX: R40.1; also elsewhere on the board
VBUS_PRIME: C20.1, R65.2, U19.6 (OUT), U19.8 (OUT), U20.6 (OUT), U20.8 (OUT); also elsewhere on the board
VBUS_SEC: C19.1, R66.2, U17.6 (OUT), U17.8 (OUT), U18.6 (OUT), U18.8 (OUT); also elsewhere on the board
VUSB: C21.1, C22.1, F1.1, J10.A4B9 (VBUS), J10.B4A9 (VBUS), U23.12 (VCC)
VUSB_POWER: F1.2, R63.2; also elsewhere on the board
V_BETA: U22.1 (VIN); also elsewhere on the board
V_HP: U21.6 (VOUT), U22.6 (VOUT); also elsewhere on the board
V_PRIME: U21.1 (VIN); also elsewhere on the board

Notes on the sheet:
USB & ISP
Check current rating!!

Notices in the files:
parts and their libraries:
SparkFun-Jumpers: Licensing: Creative Commons ShareAlike 4.0 International - https://creativecommons.org/licenses/by-sa/4.0
microbuilder: This work is placed in the public domain, and may be freely used for commercial and non-commercial work with the following conditions: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
